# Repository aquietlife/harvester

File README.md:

# Harvester

The Harvester is a hand-held, portable live sampler that lets you make music with everyday sounds. With the instrument, you are able to capture sounds around you (your voice, another musical instrument, environmental noises etc.). The instrument provides an interface that lets you play back the sampled sound based around a musical, pentatonic scale. This allows for a wildly expressive sonic palette that can be used for musical performance and sound art installations.

## Features

* Completely open-source software and hardware

* Audio I/O through onboard microphones, built-in speaker, and 1/4" output

* Gyroscope for 3-axis sensor input for affecting audio output

* Eight buttons for sample playbaack

* Recording button for sampling

* Looper button for simple looping

* Rechargable LiPo battery (completely portable and battery-powered!)

* Supports wall power/charging as well

## Videos

[Video of Harvester playing in snow](http://aquiet.life/assets/objects/harvester/harvester_snow.mov)

[Video of Harvester playing with gyroscope](https://drive.google.com/file/d/1DpVXfMJ-ruTxa6ZWckGBipXadZL-0WjP/view?usp=sharing)

[Video of Harvester playing in the Everglades](https://drive.google.com/file/d/1D1tRrY7IDSK8U0TIqJ7yX_h4CNaE4mdh/view?usp=share_link)

## Parts

A list of parts and costs can be found on this [Google Sheet](https://docs.google.com/spreadsheets/d/1hDYdzhToesEgNGzxmREglWhK1RFRyOljPsczHniATDo/edit?usp=sharing)

## Installation Instructions

### Solder up Harvester hat

* Full documentation TBD; The board itself has layouts for where compoenents should go!

### Install Raspian for Raspberry Pi

* Download the latest version of Raspian here: https://www.raspberrypi.org/downloads/raspbian/

* Install Raspian to your SD card. On OSX, you can use these instrucitons: https://www.raspberrypi.org/documentation/installation/installing-images/mac.md

* Whle the SD card is still connected, create a file called "ssh" in the boot directory of the card to enable SSH, e.g.:

`touch /Volumes/boot/ssh`

* Also, create a file called wpa_supplicant.conf in the boot directory

`vim /Volumes/boot/wpa_supplicant.conf `

* And add the following lines, replacing MySSID and MyPassword with you WiFi's network name and password:

```
ctrl_interface=DIR=/var/run/wpa_supplicant GROUP=netdev
update_config=1

network={ 
ssid="MySSID" 
psk="MyPassword" 
}
```

* Afterwards, plug your SD card into your RPI, power it on, and try to SSH into it:

`ssh pi@raspberrypi.local`

The password is `raspberry`

Then run the following command to set up your RPI to keep SSH on:

`sudo raspi-config`

Most importantly, go to Interfacing Options > SSH and enable SSH!

Select finish, then your RPi will reboot. Try connecting again and if everything is working, move on to the next section :D

### Set up Harvester Hat Hardware

** Part 1 **

* On your RPi, clone this repo

`git clone https://github.com/aquietlife/harvester`

At this point, it would probably be nice to install vim ;)

`sudo apt-get install vim`

Turn on i2s support in /boot/config.txt

`sudo vim /boot/config.txt`

Uncomment the following lines:

#dtparam=i2s=on 

#dtparam=i2c_arm=on 

#dtparam=spi=on 

#dtparam=audio=on 

Also add the following new entry:

`dtparam=i2c_vc=on`

Override bcm2708.vc_i2c_override in cmdline.txt

`sudo vim /boot/cmdline.txt`

Add the following line at the end of the line with a space after the word "consoles": 

`bcm2708.vc_i2c_override=1`

Finally enabled i2c arm from `raspi-config`

Then reboot your RPi

** Part 2 **

Start your Pi and move into the audio configuration scripts: 

`cd ~/harvester/software/custom-voice-hat/audio-config/scripts/`

Make the scripts executable: 

`sudo chmod +x ./custom-voice-hat.sh`

`sudo chmod +x ./install-i2s.sh`

Run the Executable scripts:

`sudo ./custom-voice-hat.sh`

`sudo ./install-i2s.sh` 

Run the custom-voice-hat.sh script again until you get .bak notification. 

`sudo ./custom-voice-hat.sh`

Reboot!

### Test Audio and Microphone

Test your audio:

* sudo aplay /usr/share/sounds/alsa/Front_Center.wav

Test your microphones:

* sudo arecord test.wav

* sudo aplay test.wav

### Install Python OSC server

* Install pyOSC

`pip install pyosc` 

You might also need to run it as:

`pip2 install pyosc`

### Install Pd

* Install Pd

`sudo apt-get install pd-comport`

`git clone git://github.com/umlaeute/pd-iemnet.git`

`cd pd-iemnet`

`make`

`sudo make install`

`cd ..`

* Install Pd libraries

`wget http://puredata.info/downloads/osc/releases/0.1/OSC-0.1.tar.gz`

`tar -xzvf OSC-0.1.tar.gz`

`cd OSC-0.1/`

`make`

`sudo make install`

`cd ..`

`wget http://puredata.info/downloads/osc/releases/0.2/osc-0.2.tar.gz`

`tar -xzvf osc-0.2.tar.gz`

`cd osc-0.2/`

`make`

`sudo make install`

`cd ..`
### Install Harvester Software

* Install this repo

* Test scripts manually

`python harvester/software/raspberrypi/gpio-osc.py &`

`pd -stderr -nogui -verbose -audiodev 4 harvester/software/raspberrypi/harvester.pd &`

* Celebrate!

### Autostart software

Add the following lines to the bottom of /home/pi/.bashrc

`vim /home/pi/.bashrc`

```
if pgrep -x "python" > /dev/null
then
    echo "Python is already runnning"
else
    echo "Python is not running, attempting to run Python"
	python harvester/software/raspberrypi/gpio-osc.py >/dev/null 2>&1 &
fi

if pgrep -x "pd" > /dev/null
then
    echo "Pd is already running"
else
    echo "Pd is not running, attempting to run Pd"
	pd -stderr -nogui -verbose -audiodev 4 harvester/software/raspberrypi/harvester.pd >/dev/null 2>&1 &
fi
```

## References

### Setting up Raspberry Pi

* https://desertbot.io/blog/headless-raspberry-pi-3-bplus-ssh-wifi-setup

* https://styxit.com/2017/03/14/headless-raspberry-setup.html    

* http://ivanx.com/raspberrypi/

### Misc

* https://caffinc.github.io/2016/12/raspberry-pi-3-headless/

## Credits

Voice sample: Miyu Hosoi

Circuit layout: Mark Kleeb

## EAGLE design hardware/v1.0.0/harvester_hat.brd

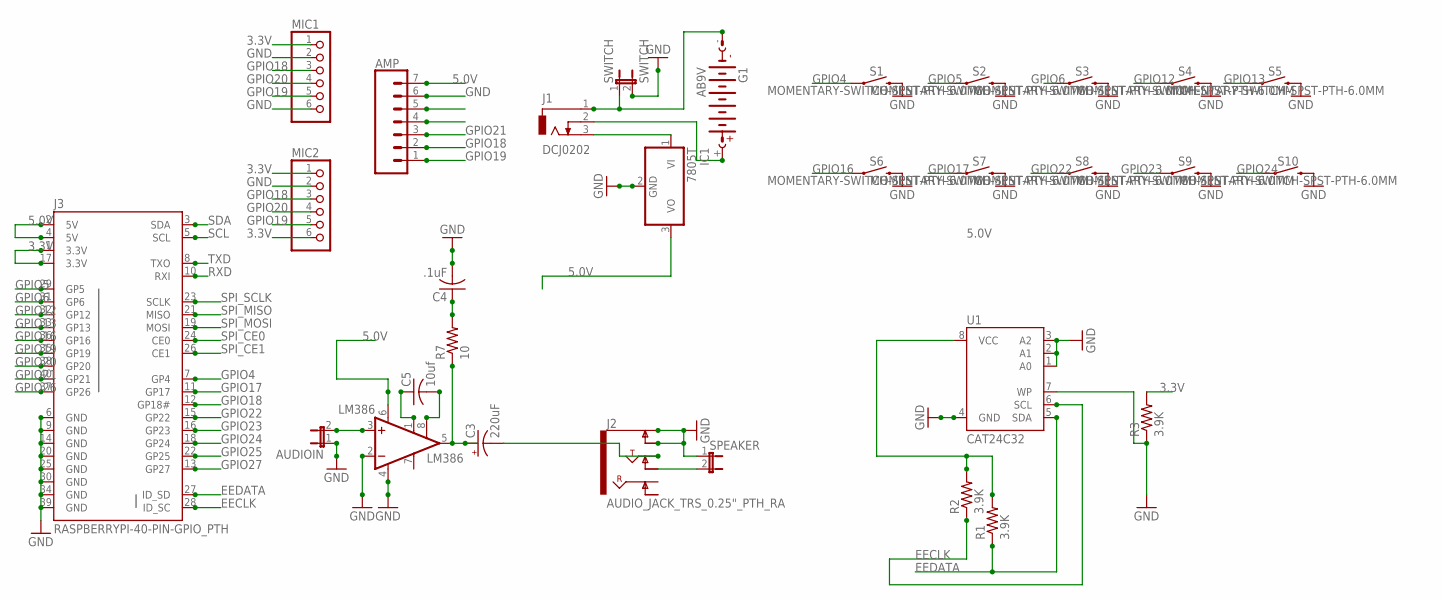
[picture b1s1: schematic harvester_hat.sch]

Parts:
AMP: CONN_07; 1X07
AUDIOIN: JP1E; JP1
C3: 220uF; E3,5-8
C4: .1uF; C025-024X044
C5: 10uf; C025-024X044
G1: AB9V
IC1: 7805T; TO220H
J1: DCJ0202
J2: AUDIO_JACK_TRS_0.25"_PTH_RA; AUDIO_JACK_0.25"_TRS_PTH_RA
J3: RASPBERRYPI-40-PIN-GPIO_PTH; 2X20_SHROUDED
LM386: LM386; DIL08
MIC1, MIC2: PINHD-1X6; 1X06
R1, R2, R3: 3.9K; 0207/10
R7: 10; 0204/7
S1, S2, S3, S4, S5, S6, S7, S8, S9, S10: MOMENTARY-SWITCH-SPST-PTH-6.0MM; TACTILE_SWITCH_PTH_6.0MM
SPEAKER: JP1E; JP1
SWITCH: SWITCH; JP1
U1: CAT24C32; DIL08

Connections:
3.3V: J3.1 (3.3V), J3.17 (3.3V), MIC1.1, MIC2.1, MIC2.6, R3.2
5.0V: AMP.7, IC1.3 (VO), J3.2 (5V), J3.4 (5V), LM386.6 (VS), R1.2, R2.2, U1.8 (VCC)
EECLK: J3.28 (ID_SC), R2.1, U1.6 (SCL)
EEDATA: J3.27 (ID_SD), R1.1, U1.5 (SDA)
GND: AMP.6, AUDIOIN.1, C4.2, IC1.2 (GND), J2.SLEEVE (EARTH), J2.SLEEVE-NORM (EARTH-NORM), J3.6 (GND), J3.9 (GND), J3.14 (GND), J3.20 (GND), J3.25 (GND), J3.30 (GND), J3.34 (GND), J3.39 (GND), LM386.2 (-IN), LM386.4 (GND), MIC1.2, MIC1.6, MIC2.2, R3.1, S1.3 (2), S2.3 (2), S3.3 (2), S4.3 (2), S5.3 (2), S6.3 (2), S7.3 (2), S8.3 (2), S9.3 (2), S10.3 (2), SPEAKER.1, SWITCH.2, U1.1 (A0), U1.2 (A1), U1.3 (A2), U1.4 (GND), U1.7 (WP)
GPIO4: J3.7 (GP4), S1.1
GPIO5: J3.29 (GP5), S2.1
GPIO6: J3.31 (GP6), S3.1
GPIO12: J3.32 (GP12), S4.1
GPIO13: J3.33 (GP13), S5.1
GPIO16: J3.36 (GP16), S6.1
GPIO17: J3.11 (GP17), S7.1
GPIO18: AMP.2, J3.12 (GP18#), MIC1.3, MIC2.3
GPIO19: AMP.1, J3.35 (GP19), MIC1.5, MIC2.5
GPIO20: J3.38 (GP20), MIC1.4, MIC2.4
GPIO21: AMP.3, J3.40 (GP21)
GPIO22: J3.15 (GP22), S8.1
GPIO23: J3.16 (GP23), S9.1
GPIO24: J3.18 (GP24), S10.1
GPIO25: J3.22 (GP25)
GPIO26: J3.37 (GP26)
GPIO27: J3.13 (GP27)
unnamed: G1.+, J1.2
unnamed: G1.-, J1.1, SWITCH.1
unnamed: IC1.1 (VI), J1.3
unnamed: AUDIOIN.2, LM386.3 (+IN)
unnamed: C5.1, LM386.1 (GAIN)
unnamed: J2.TIP-NORM, SPEAKER.2
unnamed: C3.-, J2.TIP
unnamed: C3.+, LM386.5 (OUT), R7.1
unnamed: C4.1, R7.2
unnamed: C5.2, LM386.8 (GAIN)
RXD: J3.10 (RXI)
SCL: J3.5 (SCL)
SDA: J3.3 (SDA)
SPI_CE0: J3.24 (CE0)
SPI_CE1: J3.26 (CE1)
SPI_MISO: J3.21 (MISO)
SPI_MOSI: J3.19 (MOSI)
SPI_SCLK: J3.23 (SCLK)
TXD: J3.8 (TXO)

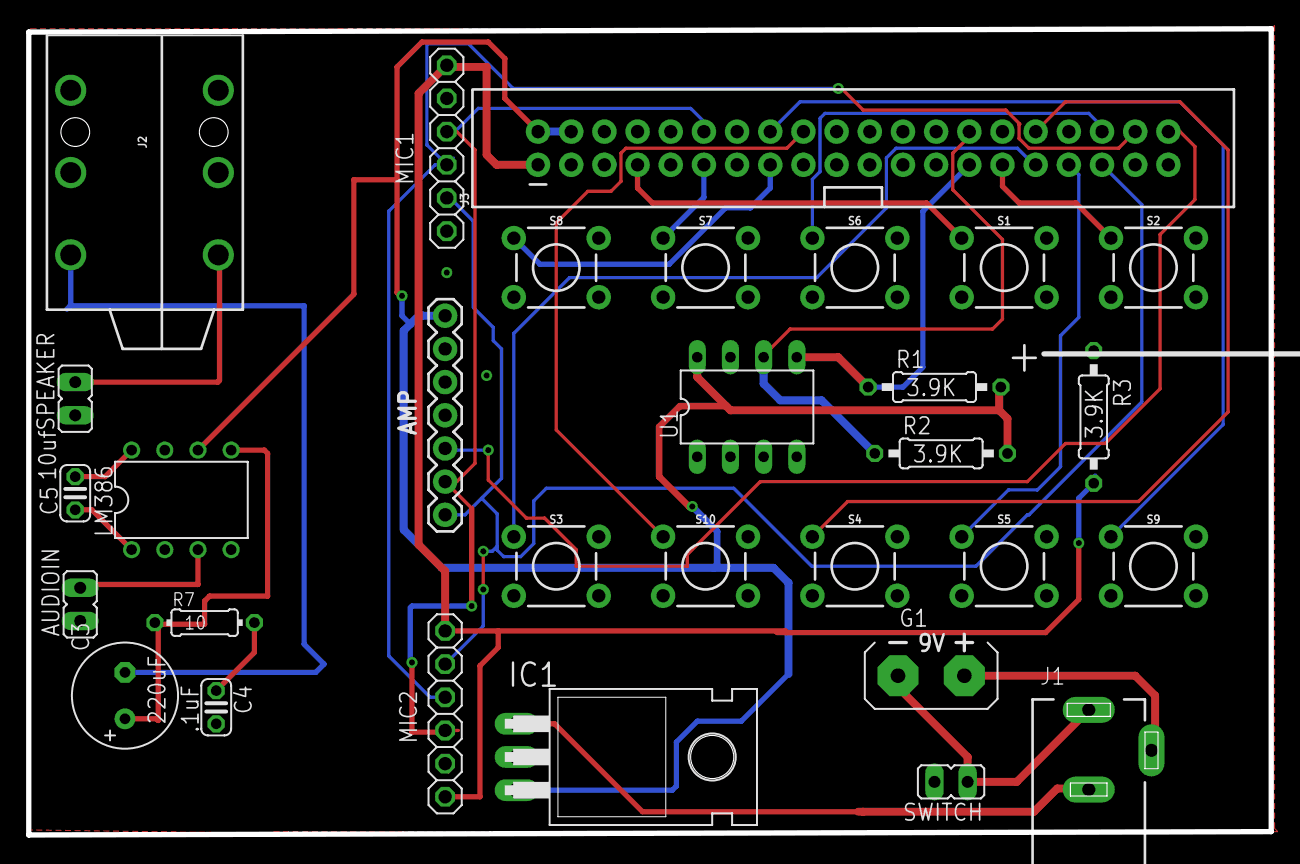
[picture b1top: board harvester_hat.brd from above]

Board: 2 copper layers, 95.1 x 61.7 mm, 30 parts (0 on the bottom side), 29 nets.

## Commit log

2018-05-08 added hardware eagle files
2018-05-28 added image
2018-05-31 added pd and python code
2018-06-02 added looper
2018-06-02 harvester pd image
2018-06-02 added extra files
2018-06-24 fixed gpio pins
2018-06-25 Fixed looper
2018-11-07 updated gitignore, hardware and hat software
2021-06-21 proof-of-concept Node.js code
2021-12-29 updated readme and chmod for scripts
2021-12-29 added bno library and replaced osc library
2021-12-30 sending gyro data to pd
2022-01-15 sending euler data, pd refactor
2022-01-22 added feedback delay
2022-01-22 added freeverb
2022-08-12 lowered volume and changed permissions
2023-02-15 updated harvester photo
2023-02-15 added new photos for harvester
2023-02-21 updated readme with features and videos
2023-02-21 updated features

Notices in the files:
parts and their libraries:
SparkFun-Switches: Licensing: Creative Commons ShareAlike 4.0 International - https://creativecommons.org/licenses/by-sa/4.0
